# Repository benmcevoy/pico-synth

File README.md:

# Raspberry Pi Pico "pico-synth"

Audio synthesizer running on a Raspberyy Pi Pico device.

Currently monophonic with TWO voices.

You WILL need to make a little circuit to drop the PWM voltage from 3.3 volts to about 1.1 volts and filter low/high noise out.  Or just risk it and plug in a speaker :)

Here is an example circuit: https://learn.adafruit.com/adding-basic-audio-ouput-to-raspberry-pi-zero/pi-zero-pwm-audio#low-pass-filter-wiring-1960165

I use `qjackctl` on linux to connect a midi keyboard via my PC.  I have not tested it directly with a MIDI controller directly attached (no PC involved), I assume it will work :)

You can find a `synth.uf2` file in the build folder which can be copied onto the Pico (hold bootsel while powering on connecting to a PC).

This is about the third C project I have written in the last thirty years, so you know... all bugs are my own.

## Pico-SDK

For PIO USB needs to be on develop, at milestone 2.1 release should be back on master.

## TinyUSB

pico-sdk ships an older version of tinyusb, so i have pulled latest of that module in order to get the newer usb host code.

Must be >= v0.17

```
# update sdk
cd pico-sdk
git submodule update --init --recursive

# update tiny-usb
cd pico-sdk/lib/tinyusb
git pull origin master
```

Run to get the dependances for pio usb.

```
python3 tools/get_deps.py rp2040
```

midi host code from:  https://github.com/rppicomidi/usb_midi_host

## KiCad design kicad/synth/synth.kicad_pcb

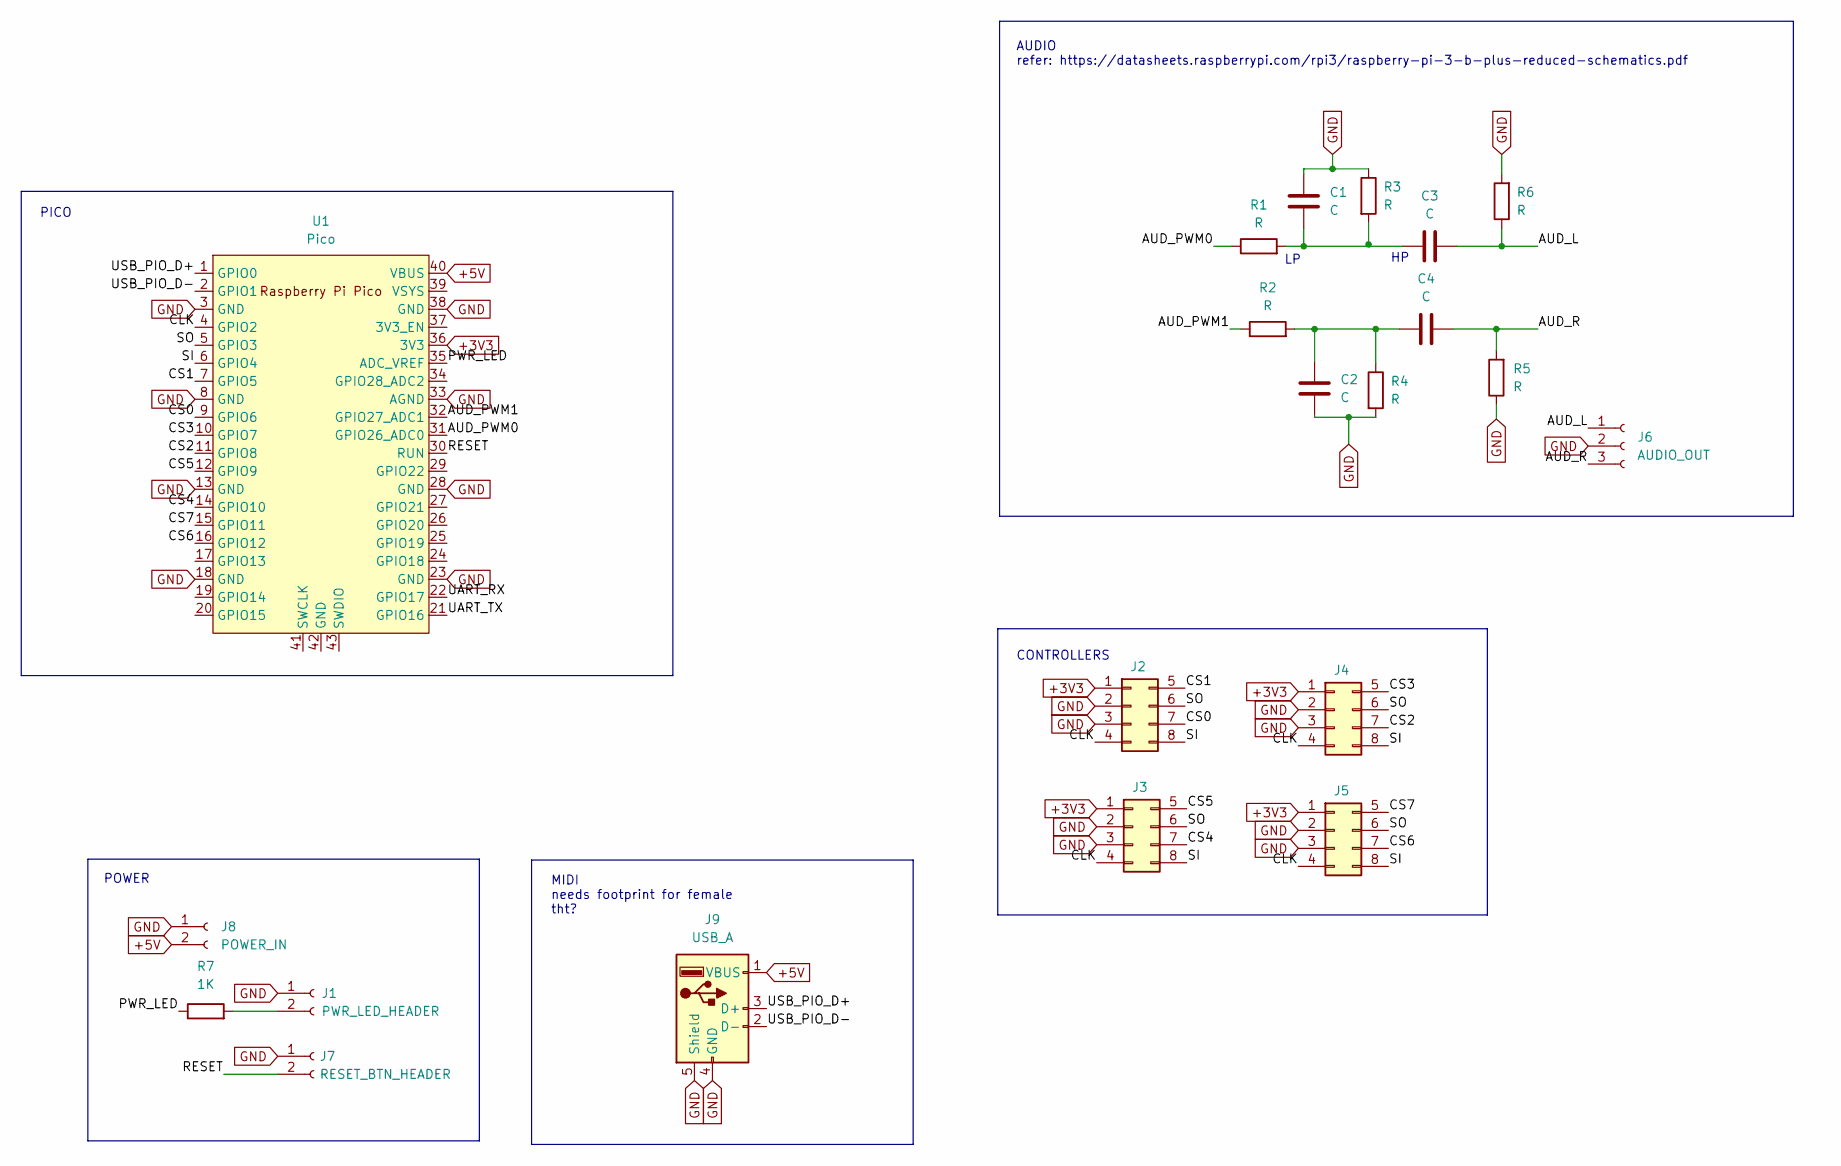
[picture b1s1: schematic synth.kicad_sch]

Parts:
C1, C2, C3, C4: C; C_0805_2012Metric_Pad1.18x1.45mm_HandSolder
J1: PWR_LED_HEADER; PinHeader_1x02_P2.54mm_Vertical
J2, J3, J4, J5: Conn_02x04_Top_Bottom; IDC-Header_2x04_P2.54mm_Vertical_SMD
J6: AUDIO_OUT; PinHeader_1x03_P2.54mm_Vertical
J7: RESET_BTN_HEADER; PinHeader_1x02_P2.54mm_Vertical
J8: POWER_IN; PinHeader_1x02_P2.54mm_Vertical
J9: USB_A; USB_A_CNCTech_1001-011-01101_Horizontal
R1, R2, R3, R4, R5, R6: R; R_0805_2012Metric_Pad1.20x1.40mm_HandSolder
R7: 1K; R_0805_2012Metric_Pad1.20x1.40mm_HandSolder
U1: Pico; RPi_Pico_SMD_TH

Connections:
+3V3: J2.1, J3.1, J4.1, J5.1, U1.36 (3V3)
+5V: J8.2, J9.1 (VBUS), U1.40 (VBUS)
/AUD_L: C3.2, J6.1, R6.1
/AUD_PWM0: R1.1, U1.31 (GPIO26_ADC0)
/AUD_PWM1: R2.1, U1.32 (GPIO27_ADC1)
/AUD_R: C4.2, J6.3, R5.2
/CLK: J2.4, J3.4, J4.4, J5.4, U1.4 (GPIO2)
/CS0: J2.7, U1.9 (GPIO6)
/CS1: J2.5, U1.7 (GPIO5)
/CS2: J4.7, U1.11 (GPIO8)
/CS3: J4.5, U1.10 (GPIO7)
/CS4: J3.7, U1.14 (GPIO10)
/CS5: J3.5, U1.12 (GPIO9)
/CS6: J5.7, U1.16 (GPIO12)
/CS7: J5.5, U1.15 (GPIO11)
/PWR_LED: R7.1, U1.35 (ADC_VREF)
/RESET: J7.2, U1.30 (RUN)
/SI: J2.8, J3.8, J4.8, J5.8, U1.6 (GPIO4)
/SO: J2.6, J3.6, J4.6, J5.6, U1.5 (GPIO3)
/UART_RX: U1.22 (GPIO17)
/UART_TX: U1.21 (GPIO16)
/USB_PIO_DI: J9.2 (D-), U1.2 (GPIO1)
/USB_PIO_DO: J9.3 (D+), U1.1 (GPIO0)
GND: C1.1, C2.2, J1.1, J2.2, J2.3, J3.2, J3.3, J4.2, J4.3, J5.2, J5.3, J6.2, J7.1, J8.1, J9.4 (GND), J9.5 (Shield), R3.1, R4.2, R5.1, R6.2, U1.3 (GND), U1.8 (GND), U1.13 (GND), U1.18 (GND), U1.23 (GND), U1.28 (GND), U1.33 (AGND), U1.38 (GND)
unnamed: C1.2, C3.1, R1.2, R3.2
unnamed: C2.1, C4.1, R2.2, R4.1
unnamed: J1.2, R7.2

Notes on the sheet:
POWER
CONTROLLERS
MIDI needs footprint for female tht?
PICO
AUDIO refer: https://datasheets.raspberrypi.com/rpi3/raspberry-pi-3-b-plus-reduced-schematics.pdf

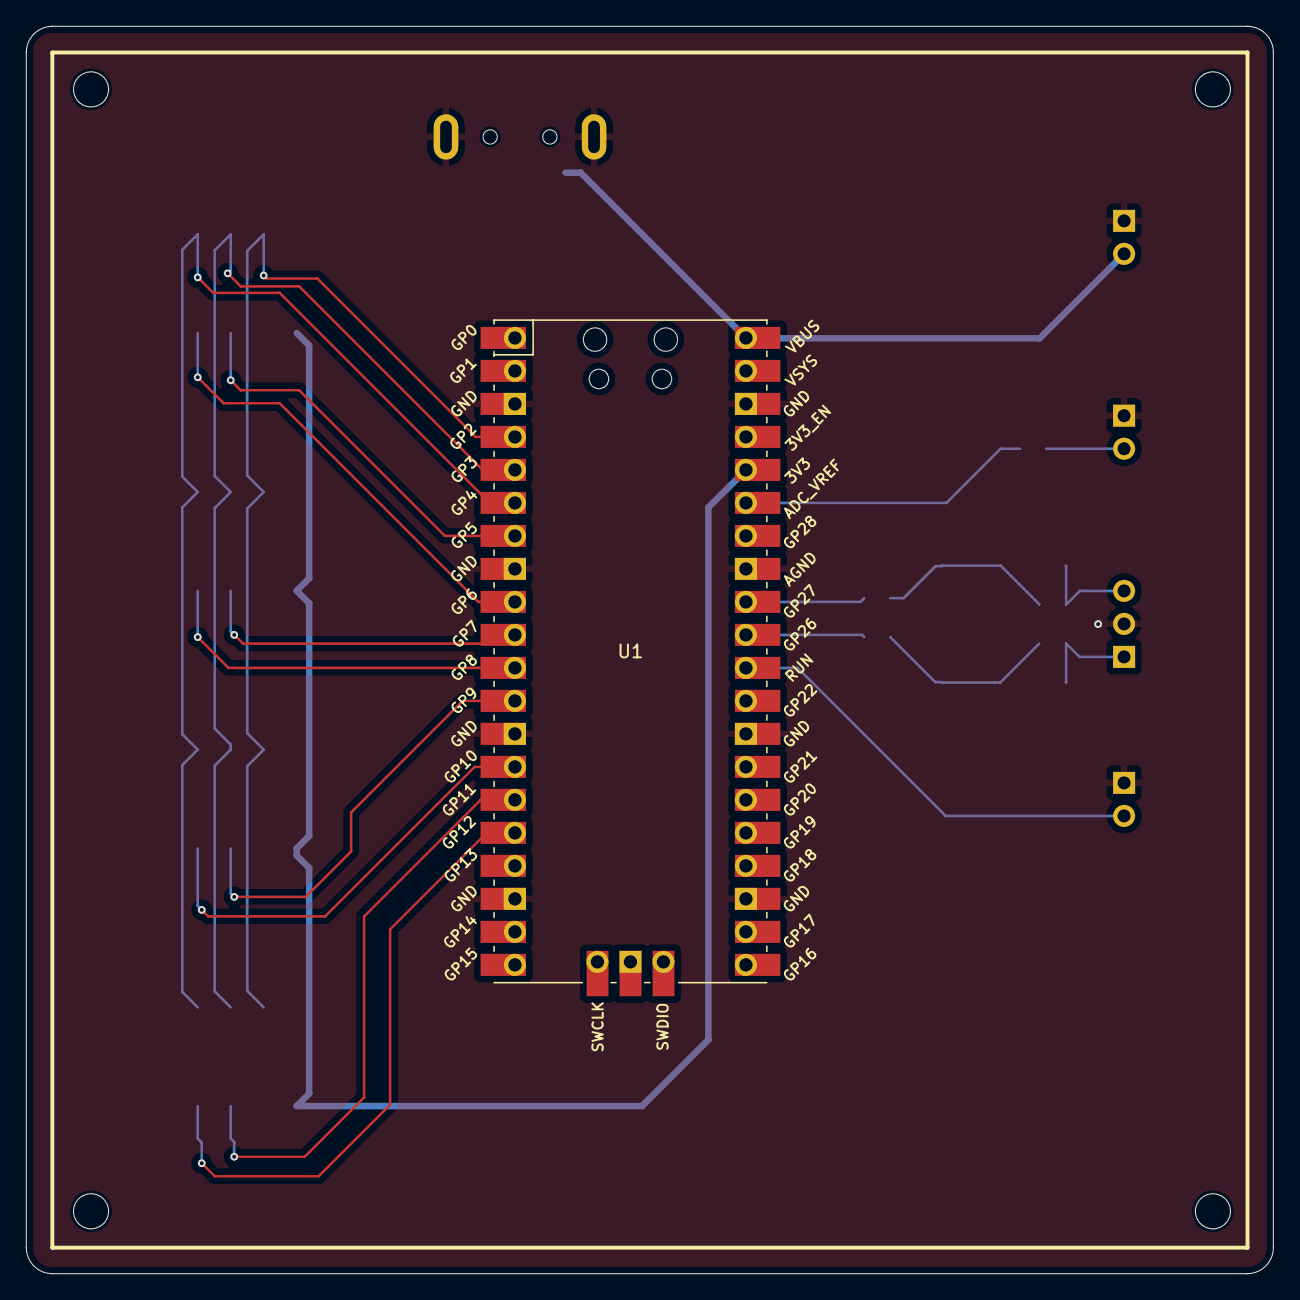
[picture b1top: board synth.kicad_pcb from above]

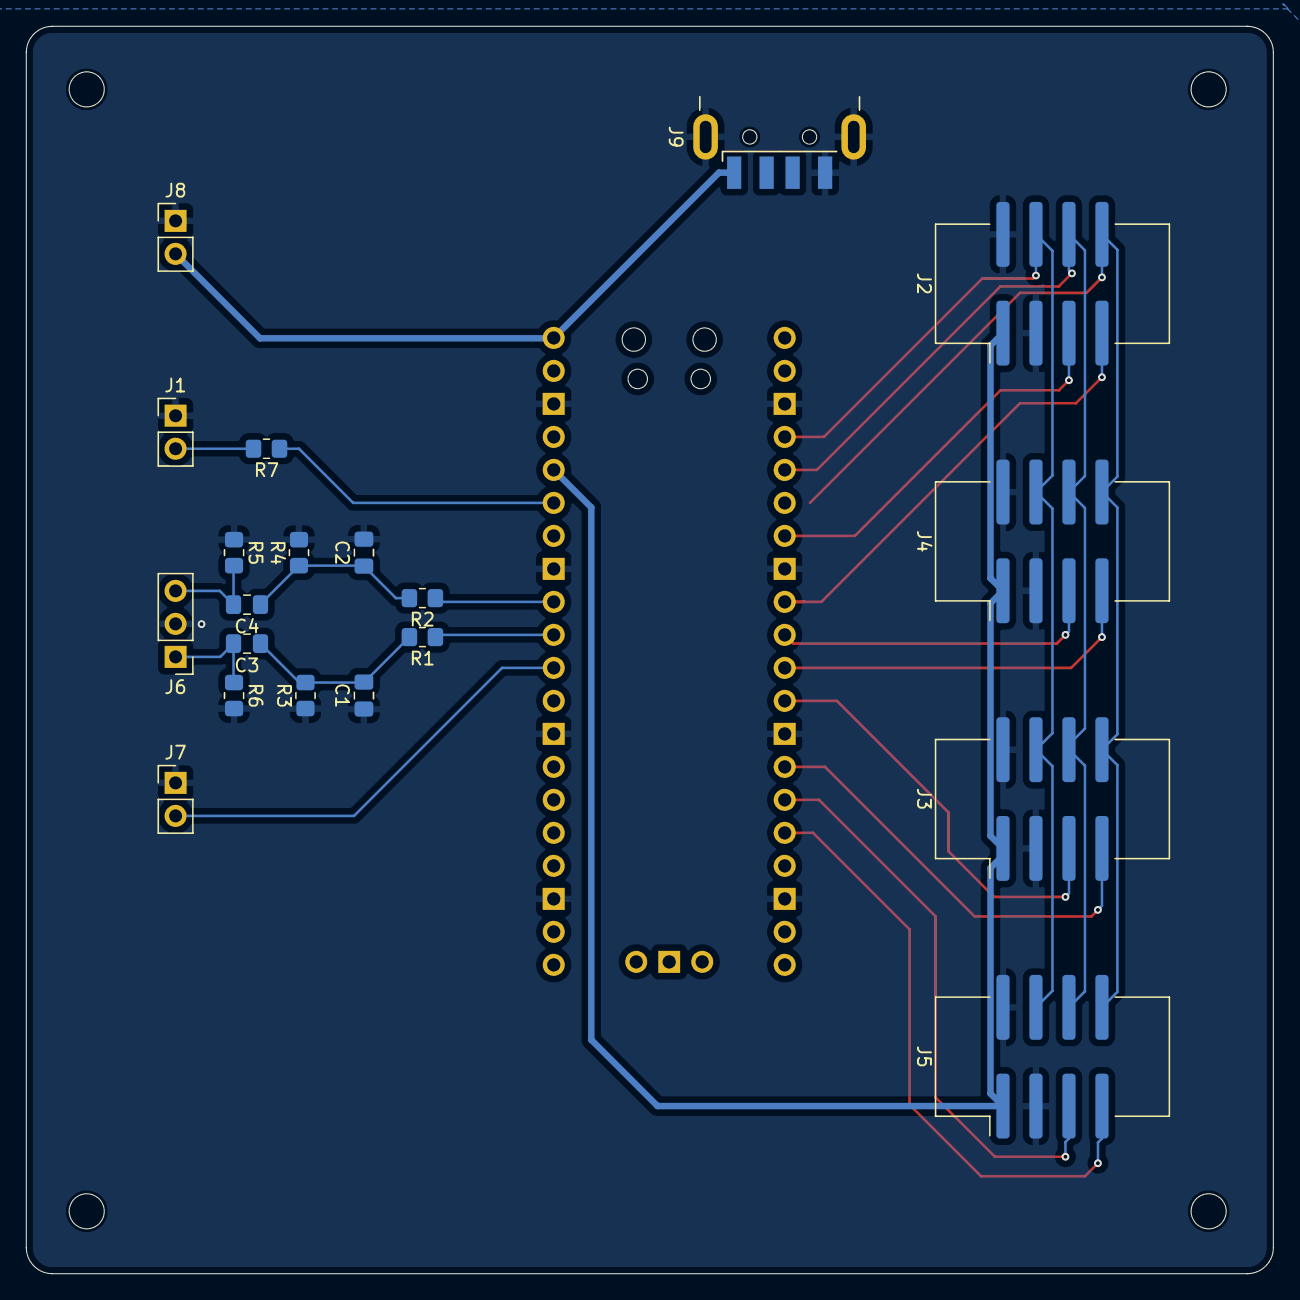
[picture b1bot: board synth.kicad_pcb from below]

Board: 2 copper layers, 96.0 x 96.0 mm, 25 parts (20 on the bottom side), 25 nets.

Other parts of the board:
H1, H2, H3, H4: MountingHole; MountingHole_2.7mm_M2.5

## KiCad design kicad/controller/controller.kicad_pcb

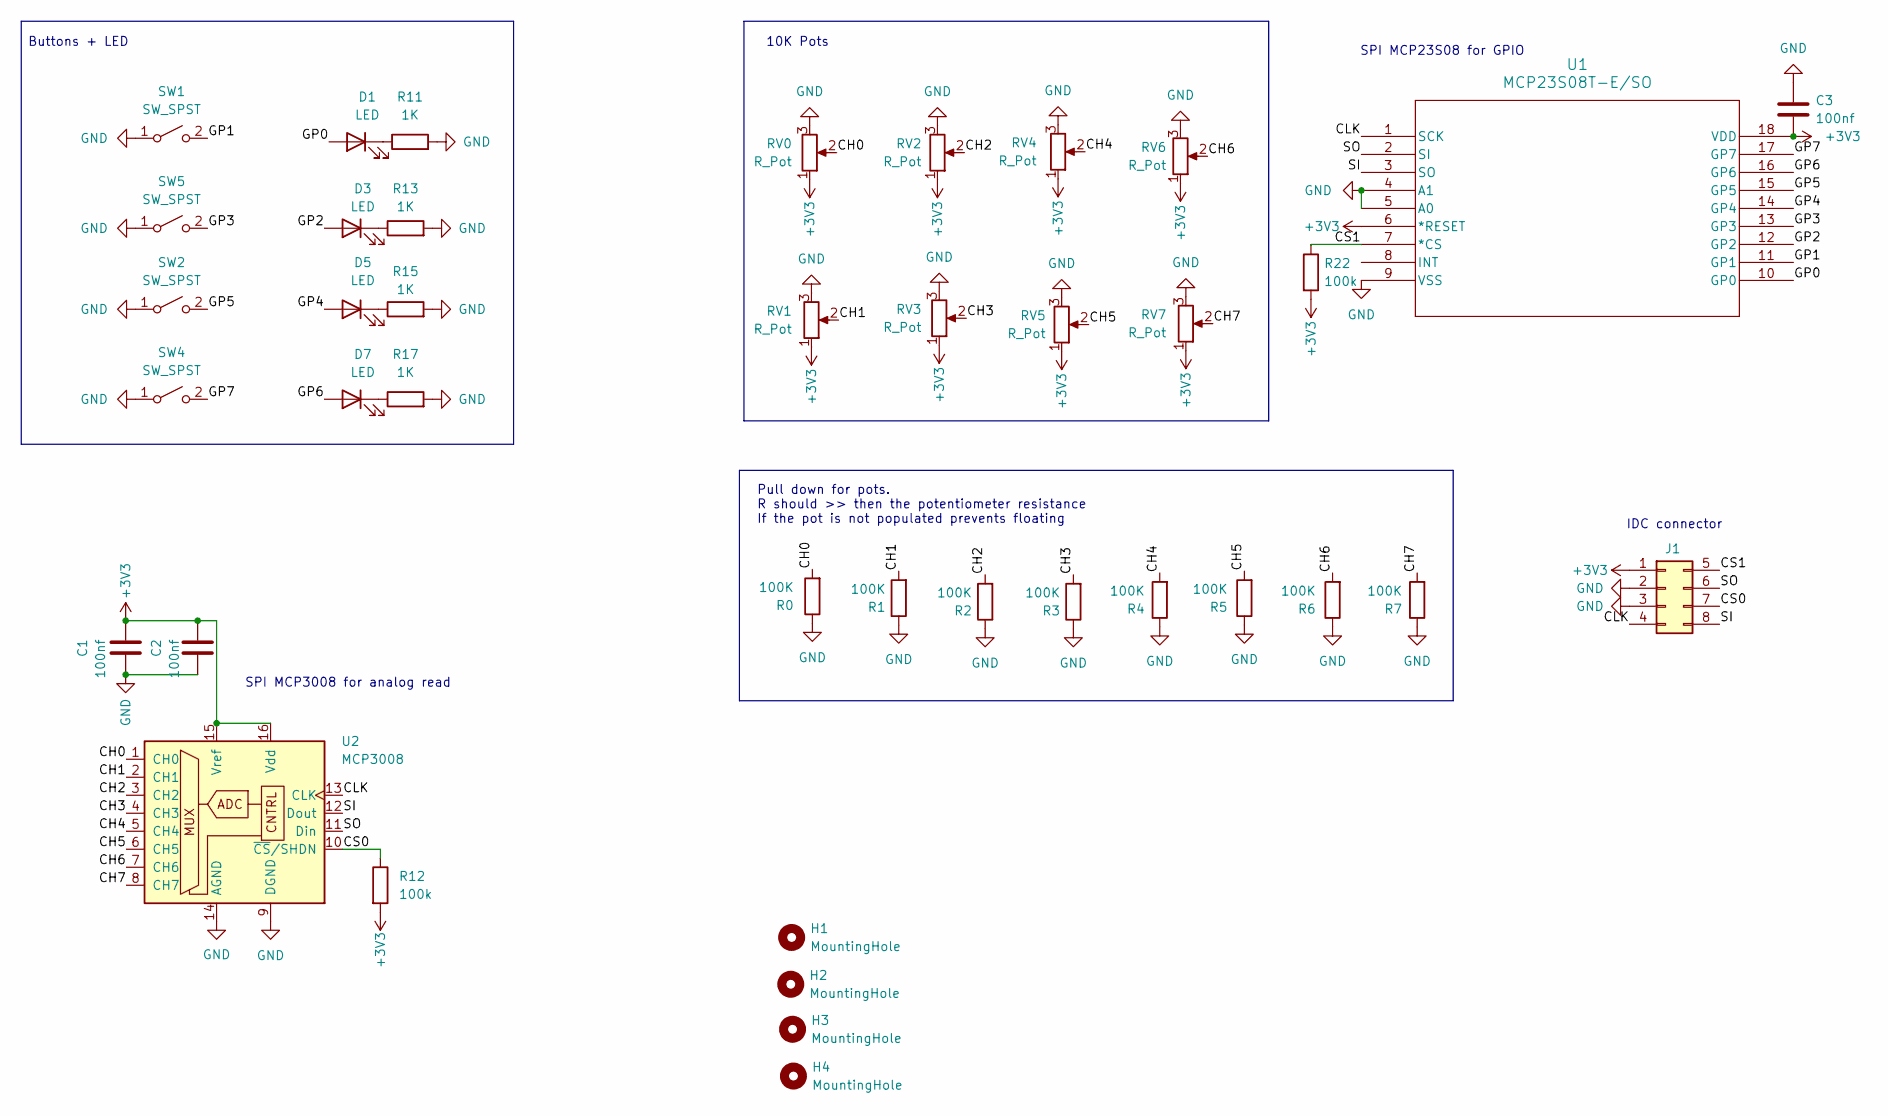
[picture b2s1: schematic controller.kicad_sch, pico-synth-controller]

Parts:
C1, C2, C3: 100nf; C_0805_2012Metric
D1, D3, D5, D7: LED; LED_D3.0mm_FlatTop
H1, H2, H3, H4: MountingHole; MountingHole_2.7mm_M2.5
J1: Conn_02x04_Top_Bottom; IDC-Header_2x04_P2.54mm_Vertical_SMD
R0, R1, R2, R3, R4, R5, R6, R7: 100K; R_0805_2012Metric
R11, R13, R15, R17: 1K; R_0805_2012Metric
R12, R22: 100k; R_0805_2012Metric
RV0, RV1, RV2, RV3, RV4, RV5, RV6, RV7: R_Pot; Potentiometer_Bourns_PTV09A-1_Single_Vertical
SW1, SW2, SW4, SW5: SW_SPST; SW_PUSH-12mm
U1: MCP23S08T-E/SO; SOIC18-W_MC_MCH
U2: MCP3008; SOIC-16_3.9x9.9mm_P1.27mm

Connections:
+3V3: C1.2, C2.2, C3.2, J1.1, R12.2, R22.2, RV0.1, RV1.1, RV2.1, RV3.1, RV4.1, RV5.1, RV6.1, RV7.1, U1.6 (*RESET), U1.18 (VDD), U2.15 (Vref), U2.16 (Vdd)
/CH0: R0.2, RV0.2, U2.1 (CH0)
/CH1: R1.2, RV1.2, U2.2 (CH1)
/CH2: R2.2, RV2.2, U2.3 (CH2)
/CH3: R3.2, RV3.2, U2.4 (CH3)
/CH4: R4.2, RV4.2, U2.5 (CH4)
/CH5: R5.2, RV5.2, U2.6 (CH5)
/CH6: R6.2, RV6.2, U2.7 (CH6)
/CH7: R7.2, RV7.2, U2.8 (CH7)
/CLK: J1.4, U1.1 (SCK), U2.13 (CLK)
/CS0: J1.7, R12.1, U2.10 (~CS/SHDN)
/CS1: J1.5, R22.1, U1.7 (*CS)
/GP0: D1.2 (A), U1.10 (GP0)
/GP1: SW1.2 (B), U1.11 (GP1)
/GP2: D3.2 (A), U1.12 (GP2)
/GP3: SW5.2 (B), U1.13 (GP3)
/GP4: D5.2 (A), U1.14 (GP4)
/GP5: SW2.2 (B), U1.15 (GP5)
/GP6: D7.2 (A), U1.16 (GP6)
/GP7: SW4.2 (B), U1.17 (GP7)
/SI: J1.8, U1.3 (SO), U2.12 (Dout)
/SO: J1.6, U1.2 (SI), U2.11 (Din)
GND: C1.1, C2.1, C3.1, J1.2, J1.3, R0.1, R1.1, R2.1, R3.1, R4.1, R5.1, R6.1, R7.1, R11.2, R13.2, R15.2, R17.2, RV0.3, RV1.3, RV2.3, RV3.3, RV4.3, RV5.3, RV6.3, RV7.3, SW1.1 (A), SW2.1 (A), SW4.1 (A), SW5.1 (A), U1.4 (A1), U1.5 (A0), U1.9 (VSS), U2.9 (DGND), U2.14 (AGND)
unnamed: D1.1 (K), R11.1
unnamed: D3.1 (K), R13.1
unnamed: D5.1 (K), R15.1
unnamed: D7.1 (K), R17.1

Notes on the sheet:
10K Pots
Buttons + LED
Pull down for pots. R should >> then the potentiometer resistance If the pot is not populated prevents floating
IDC connector
SPI MCP23S08 for GPIO
SPI MCP3008 for analog read

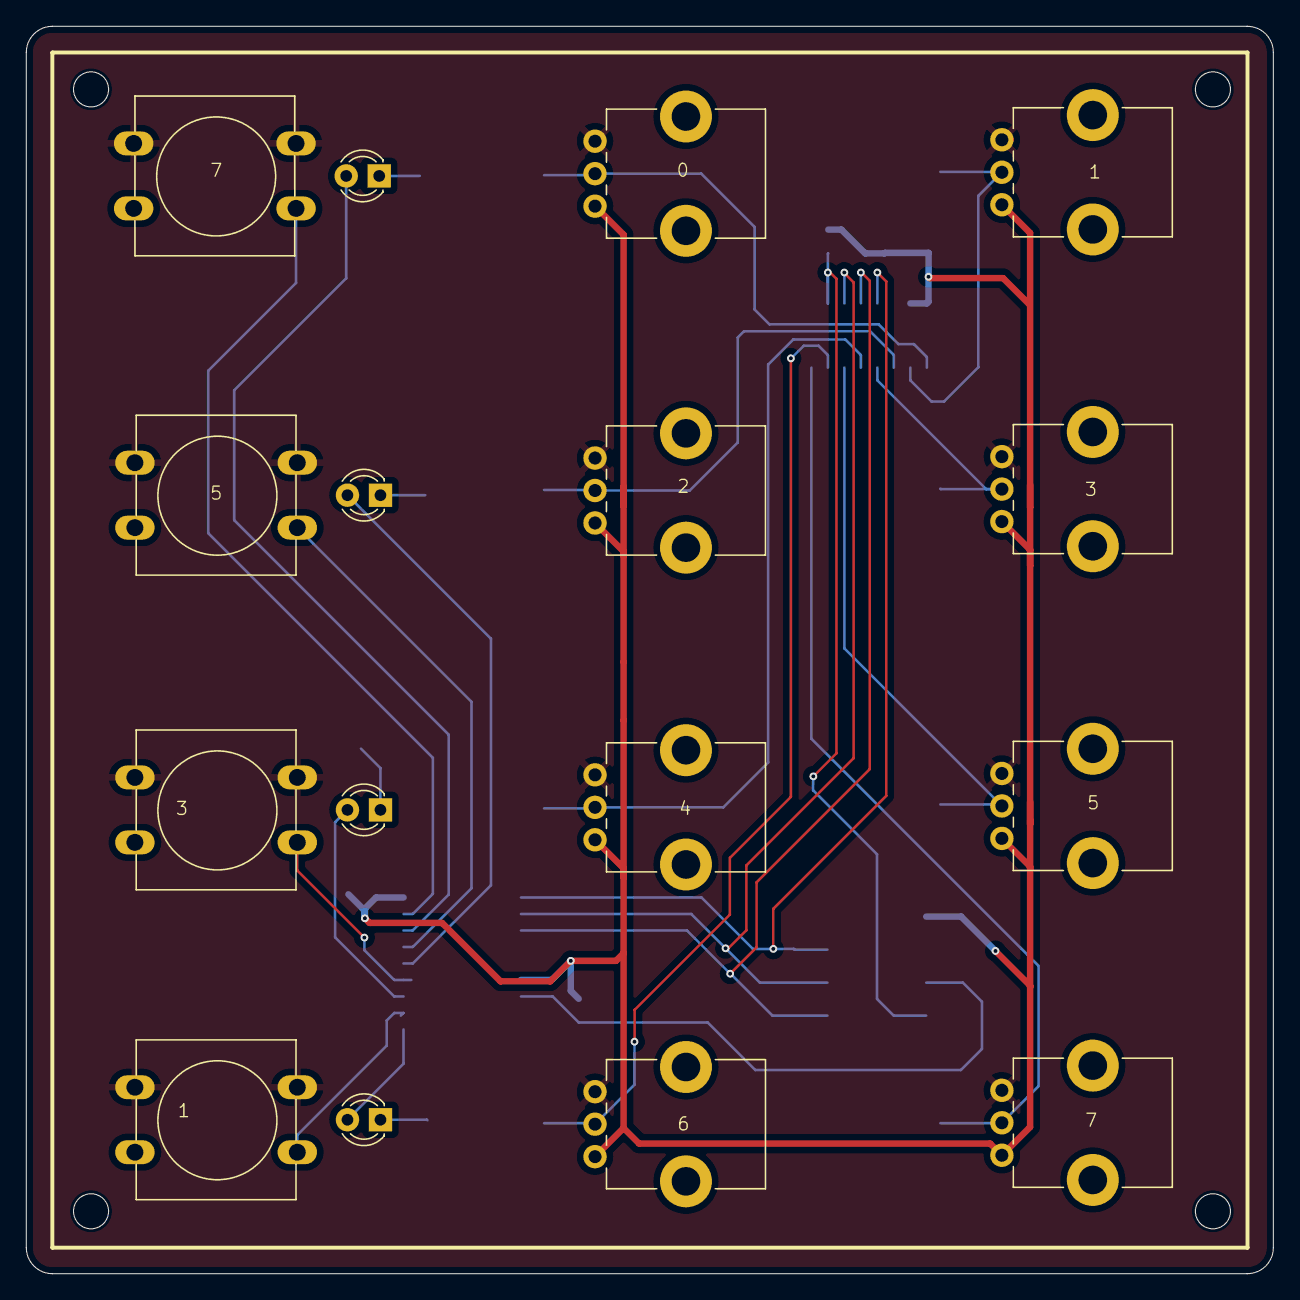
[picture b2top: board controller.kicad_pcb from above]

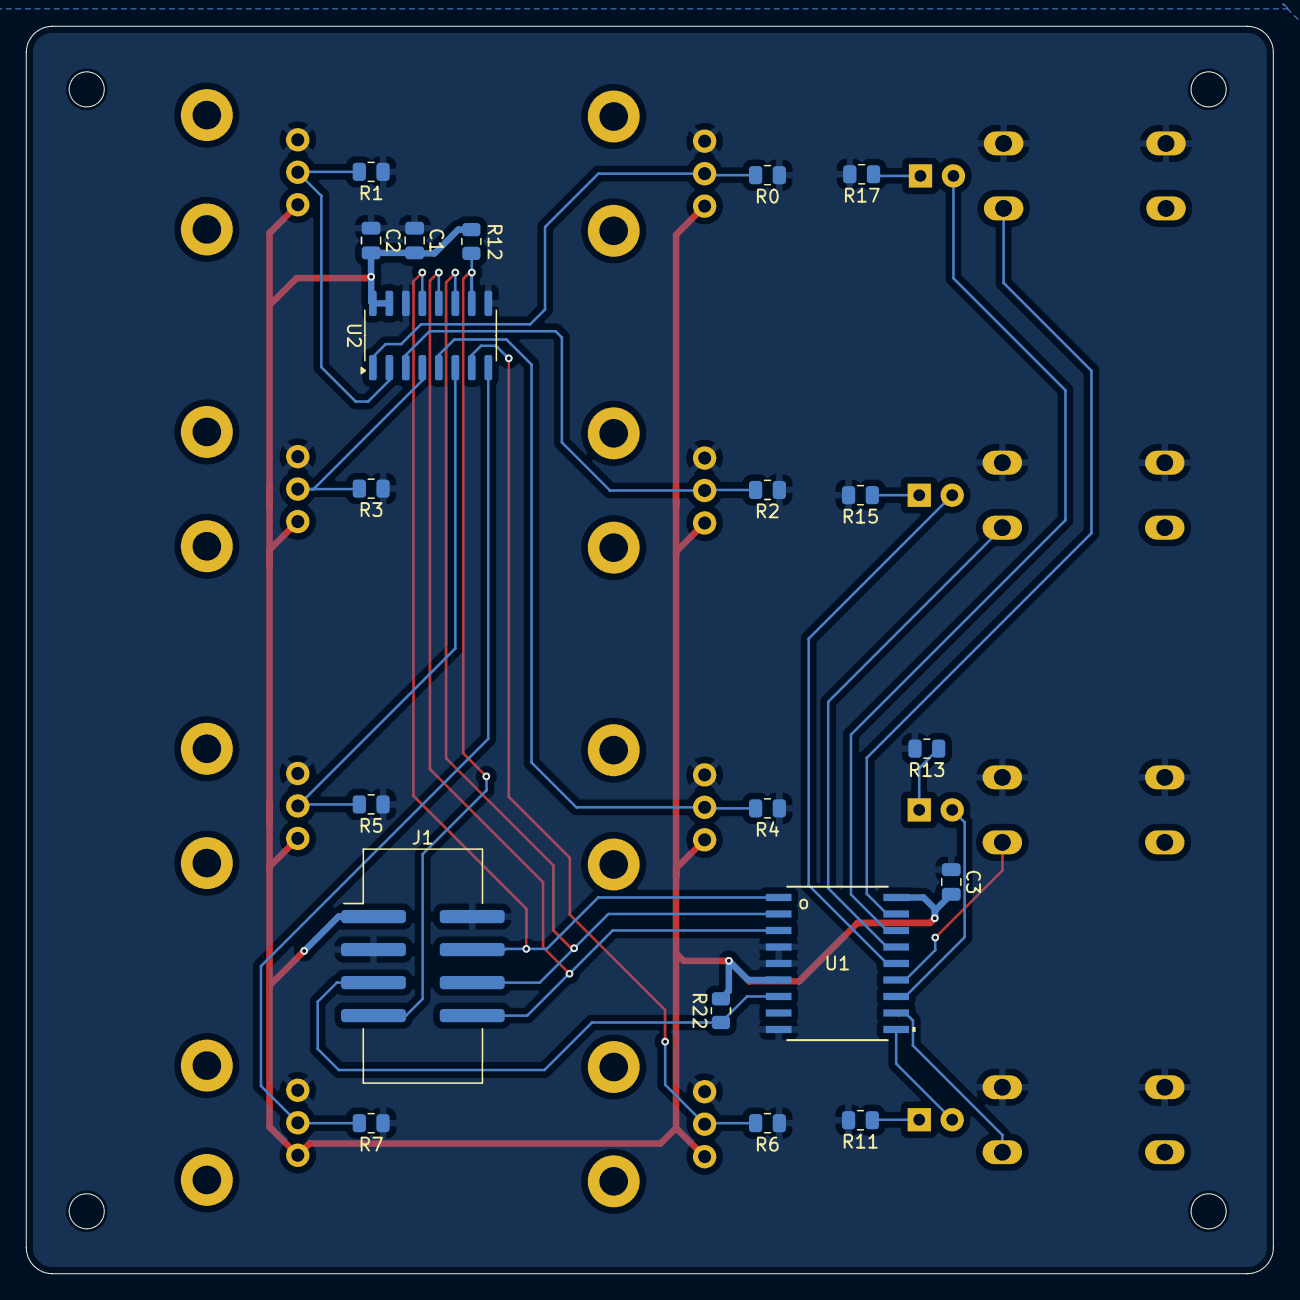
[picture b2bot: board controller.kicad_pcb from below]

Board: 2 copper layers, 96.0 x 96.0 mm, 40 parts (20 on the bottom side), 27 nets.

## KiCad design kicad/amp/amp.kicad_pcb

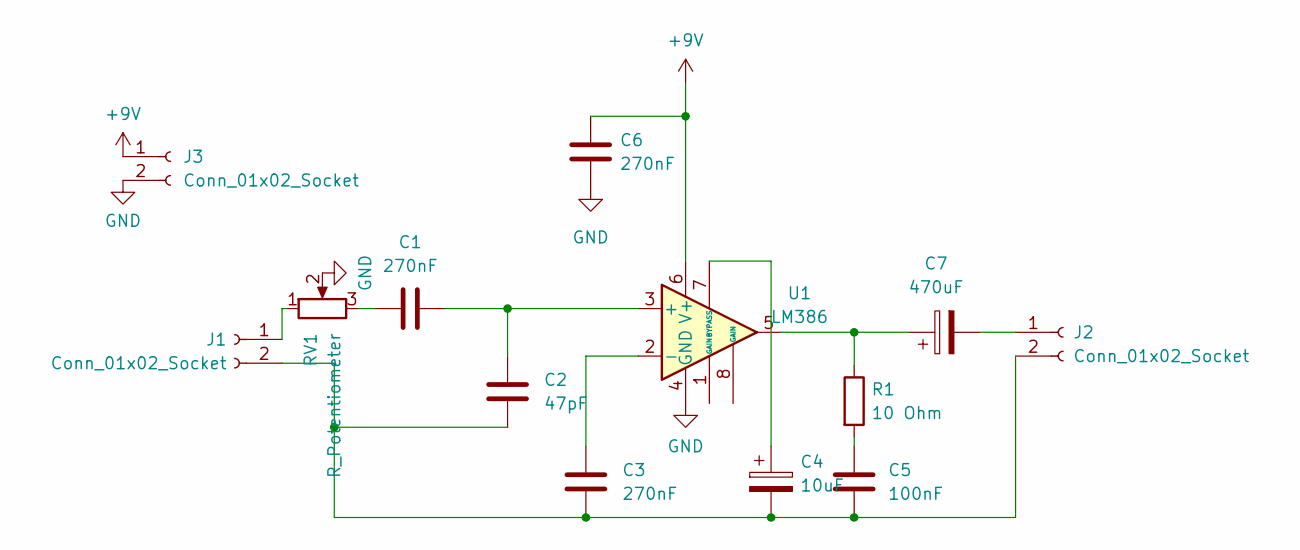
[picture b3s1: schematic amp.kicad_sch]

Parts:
C1, C3, C6: 270nF; C_Rect_L18.0mm_W5.0mm_P15.00mm_FKS3_FKP3
C2: 47pF; FKP2_04.5WX06.0HX07.2L_WIM
C4: 10uF; CP_Radial_D8.0mm_P3.50mm
C5: 100nF; C_Disc_D5.0mm_W2.5mm_P2.50mm
C7: 470uF; CP_Radial_D8.0mm_P3.50mm
J1, J2, J3: Conn_01x02_Socket; PinHeader_1x02_P2.54mm_Vertical
R1: 10 Ohm; R_Axial_DIN0204_L3.6mm_D1.6mm_P7.62mm_Horizontal
RV1: R_Potentiometer; Potentiometer_Alps_RK09K_Single_Vertical
U1: LM386; N08E_TEX

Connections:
+9V: C6.1, J3.1, U1.6 (V+)
GND: C6.2, J3.2, RV1.2, U1.4 (GND)
unnamed: C1.1, RV1.3
unnamed: C5.1, R1.2
unnamed: C7.1, R1.1, U1.5
unnamed: J1.1, RV1.1
unnamed: C2.2, C3.2, C4.2, C5.2, J1.2, J2.2
unnamed: C7.2, J2.1
unnamed: C1.2, C2.1, U1.3 (+)
unnamed: C3.1, U1.2 (-)
unnamed: C4.1, U1.7 (BYPASS)

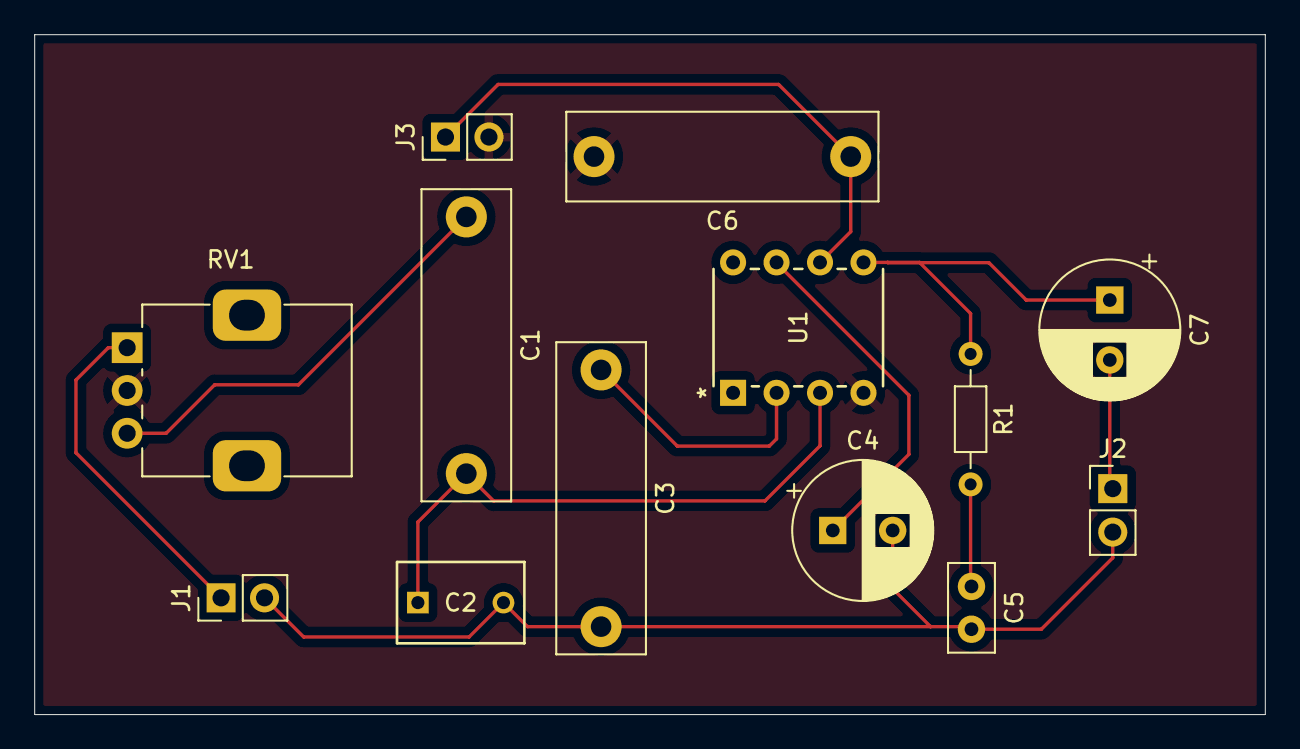
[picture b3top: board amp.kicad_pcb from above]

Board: 2 copper layers, 71.9 x 39.7 mm, 13 parts (0 on the bottom side), 11 nets.

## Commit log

2023-07-09 init
2023-07-11 tidy up into context struct
2023-07-11 use DMA to send data to PWM
2023-07-11 remove unused library in cmake
2023-07-14 start sketching out waveforms
2023-07-14 noise works :) triangle sounds whack
2023-07-16 simplify my use of a pointer to current buffer. Debugging why trianlge goes click? no idea...
2023-07-17 add more waveforms. triangle still clicky, but oh well. add a voice and play a little loop
2023-07-18 fixed silly triangle wave issues
2023-07-19 use wavetables instead for better performance and more deterministic timing
2023-07-19 convert to float to align with 32bit processor
2023-07-19 watched some videos on how to write c... lol
2023-07-20 yoink, obviously need to learn more c :)
2023-07-22 envelope generation, loosely based on my old c# code. I tried using funciton pointers to mimic the FP approach and it as quite confusing... ending up with a state machine
2023-07-22 update the development notes
2023-07-23 get UART and SWD working
2023-07-24 some basic midi support :)
2023-07-24 set next goals as headers
2023-07-25 monophonic using three voices/oscillators. dodgy note priority and detune
2023-07-26 add low pass filter and some MIDI cc to control it
2023-07-27 getting a clue
2023-07-27 just mucking around, wired in a few more midi CC knobs
2023-08-03 bit of an overhaul to use fixed point. not quite finished and there are few odd artifacts, but performance is looking good
2023-08-03 more fixed point. I have given up on the filter for now as it sounds bad. I can now achieve a high rate of over 300kHz and the sound is pretty decent.
2023-08-06 fix bug in envelope, needed an epsilon(?) value as we would not always be exactly == 0. change pwm clock to target a sample rate, this increases the bit depth to 13 bits which sounds nicer
2023-08-08 add some delay and wire in some midi to control it
2023-08-08 improve the note priority to something sane
2023-08-09 remove more floats
2023-08-10 tweaking things and see what performance I can get - hitting 20 oscillators at 32767Hz. thinking about how I could use the second core
2023-08-12 playing with gating
2023-08-12 fixing the bugs i just added
2023-08-13 the no_flash option is RAM only and led to much confusion for me. Let's actually update the firmware instead...
2023-08-13 experimenting with the hardware interpolator
2023-08-13 fixed test code so at least it's a working example
2023-08-14 another bug maybe i need more types
2023-08-14 DRY up envelope and gate
2023-08-17 add tempo to start providing beats/clock. added metronome using this. my metronome implementation seems overly complex, but whatevs. tempo should allow step seqeuncer and arpeggiator
2023-08-18 mucking around, try some dithering
2024-06-24 sketching out start of controller
2024-06-25 wire in a few pots
2024-06-28 tidying up controller actions
2024-06-29 trying to align to clang code standard
2024-06-30 about to try and add usb midi host
2024-06-30 can now plug midi keyboard in directly
2024-06-30 tidy up midi host changes
2024-07-01 saw wave was wrong!
2024-07-01 get the filter working somewhat
2024-07-01 i can't remeber
2024-07-01 rework the main pipeline that generates sound and check filter+delay+metronome is ok
2024-07-01 cite usb host code
2024-07-02 fix some bugs and add pitch bend. broke square wave
2024-07-02 move some functions for better cohesion
2024-07-02 refactor a little
2024-07-02 fix bug
2024-07-02 fix squarewave and add pulse width
2024-07-02 refactor, move concerns to structs
2024-07-06 fidlde with delay and make it more like the bela example as that one works betterer
2024-07-06 ignore kicad back files
2024-07-06 tweak delay less glitchy
2024-07-06 tidy
2024-07-08 begin refactoring voice to a set of oscillators. add dry/wet mix to delay. sketching out a generic UI pcb
2024-07-08 update ignore
2024-07-09 fix some bugs in the delay wet/dy and in the pitch bend
2024-07-10 fix bug with the detune as it is addition and no longer a multiplication
2024-07-11 tweak metronome and make a LED blink
2024-07-11 trying to add USB host and device simultaneously
2024-07-11 reduce buffer length for less latency, not that I can tell any difference...
2024-07-15 sketch out LM386 amp
2024-08-13 start adding mcp23s08 gpio extender
2024-08-14 starting to get control over the mcp23s08:
2024-08-15 toggle and momentry work as intended
2024-08-17 fix side-set logic - bool is NOT a char!
2024-09-06 fix button behaviour now I have a PCB
2024-09-10 fiddling with the config as I test the PCB
2024-09-10 removed debounce as in practice it did not help
2024-09-11 move uart pins and prepare for PIO USB
2024-09-20 USB PIO now works and can control via PC or direct MIDI device :)
